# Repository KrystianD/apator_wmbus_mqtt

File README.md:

# Apator WMBus reader

CC1101-based WMBus reader for Apator AT-WMBUS-16-2 water volume meters for Linux-based SBCs.
Uses `spidev` for communication with CC1101 module and `gpio-cdev` for RX FIFO-ready interrupt handling.

The repository contains:

* CC1101 hat designed for Orange Pi Zero 3 - KiCad board,
* Rust library for interfacing with CC1101 module,
* Rust application for receiving and decoding WMBus messages using CC1101 and publishing readings to MQTT broker.

## Board

## Resources

### CC1101
* https://github.com/fphammerle/python-cc1101 - Python interface for CC1101
* [Using CC1101 for WMBus reception (PDF)](https://www.ti.com/lit/an/swra234a/swra234a.pdf) - TI
* https://github.com/dsvensson/cc1101
* [CC1101 Datasheet](https://www.ti.com/lit/ds/symlink/cc1101.pdf)

### WMBus
* https://github.com/wmbusmeters/wmbusmeters - Decoding
* [WMBus frame formats (PDF)](https://www.ti.com/lit/an/swra522e/swra522e.pdf) - TI
* [WMBus frame formats (PDF)](https://www.ti.com/lit/an/swra234a/swra234a.pdf) - TI
* [WMBus frame formats (PDF)](https://www.st.com/resource/en/application_note/an4772-wmbus-2013-firmware-stack-overview-stmicroelectronics.pdf) - ST

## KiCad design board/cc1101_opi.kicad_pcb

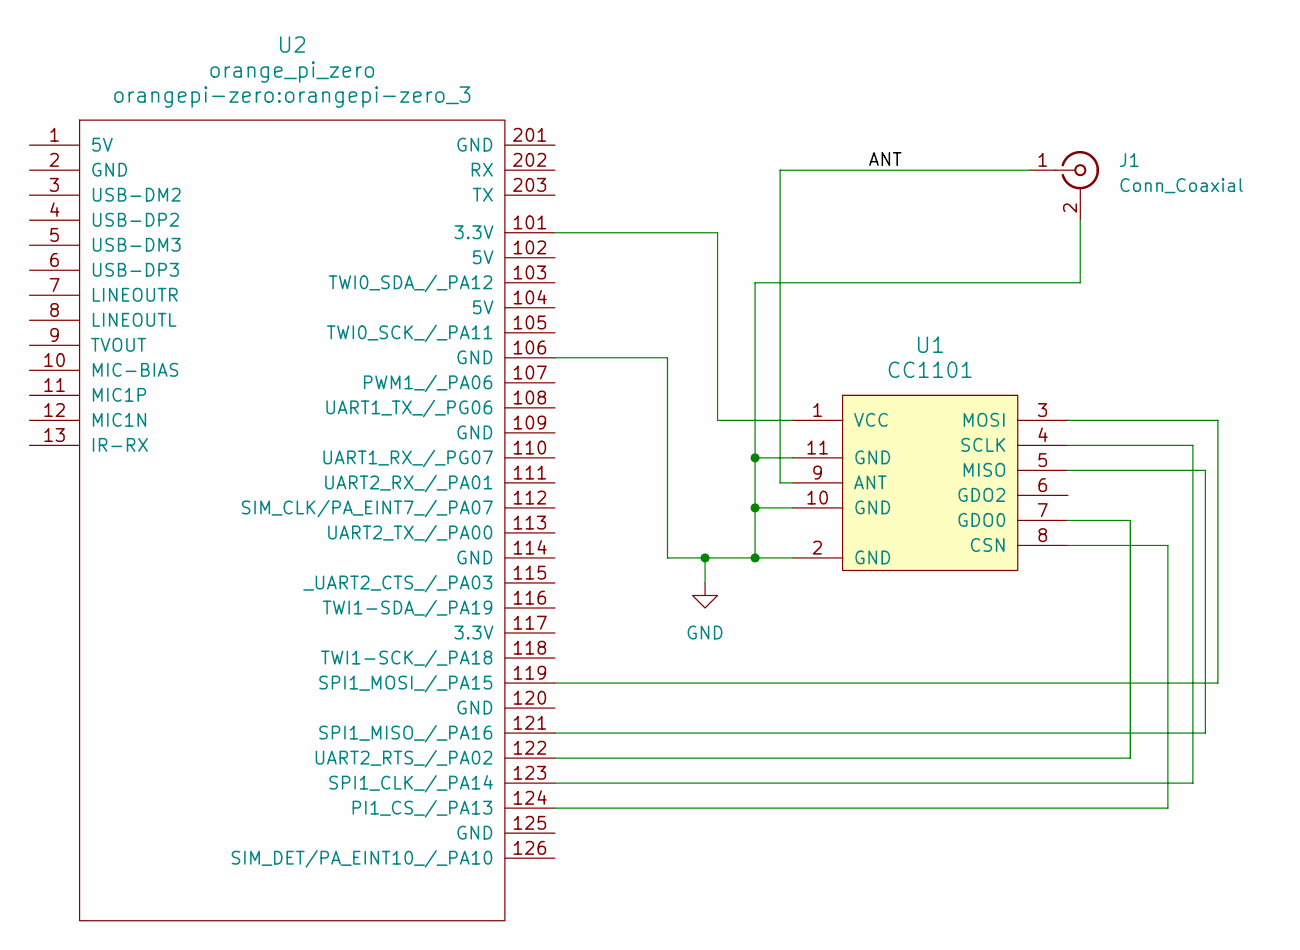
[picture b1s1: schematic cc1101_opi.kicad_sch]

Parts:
J1: Conn_Coaxial; SMA_Amphenol_132134-11_Vertical
U1: CC1101; CC1101_SMD
U2: orange_pi_zero; orangepi-zero_3

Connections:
/ANT: J1.1 (In), U1.9 (ANT)
GND: J1.2 (Ext), U1.2 (GND), U1.10 (GND), U1.11 (GND), U2.106 (GND)
unnamed: U1.8 (CSN), U2.124 (PI1_CS_/_PA13)
unnamed: U1.7 (GDO0), U2.122 (UART2_RTS_/_PA02)
unnamed: U1.5 (MISO), U2.121 (SPI1_MISO_/_PA16)
unnamed: U1.3 (MOSI), U2.119 (SPI1_MOSI_/_PA15)
unnamed: U1.4 (SCLK), U2.123 (SPI1_CLK_/_PA14)
unnamed: U1.1 (VCC), U2.101 (3.3V)

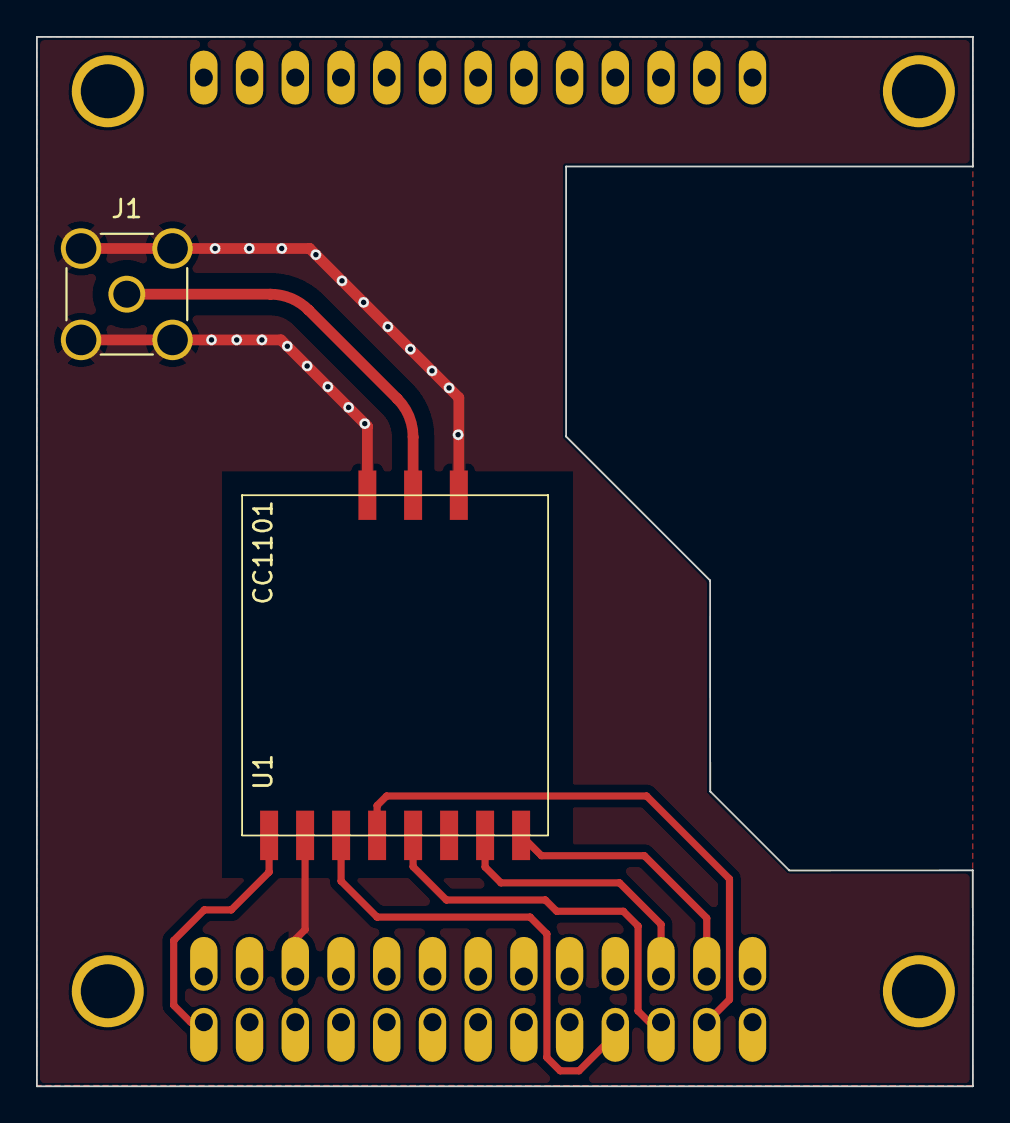
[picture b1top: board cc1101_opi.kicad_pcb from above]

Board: 2 copper layers, 52.0 x 58.3 mm, 3 parts (1 on the bottom side), 8 nets.
